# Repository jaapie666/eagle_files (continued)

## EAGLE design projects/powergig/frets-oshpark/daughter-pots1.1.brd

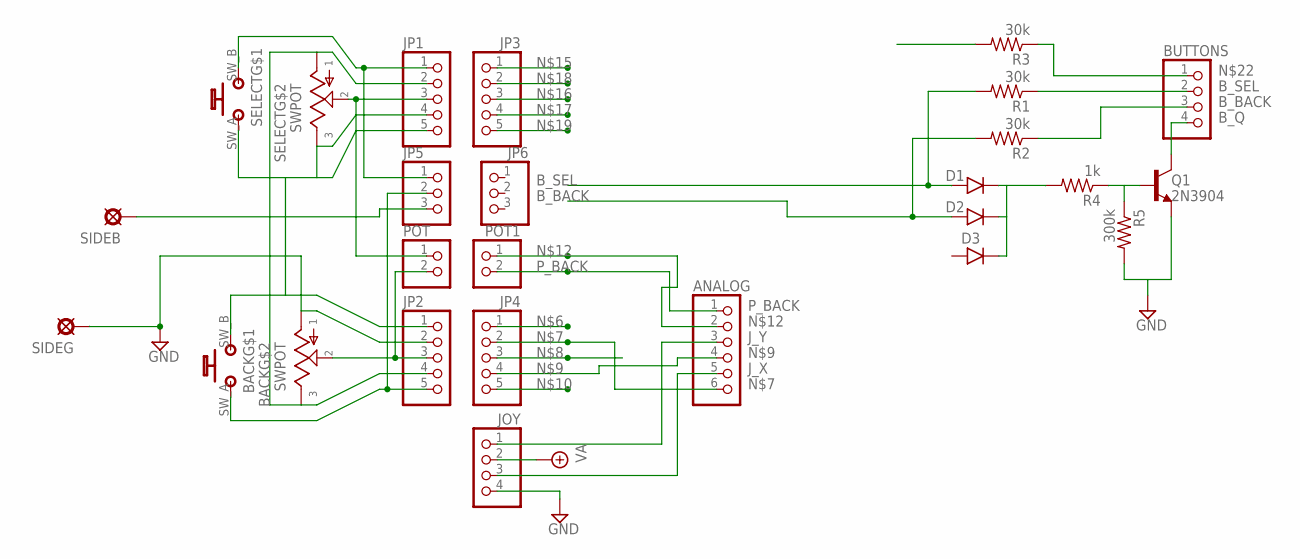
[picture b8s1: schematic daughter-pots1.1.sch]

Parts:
ANALOG: PINHD-1X6; 1X06
BACK: SWPOT
BUTTONS: PINHD-1X4; 1X04
D1: 1N4148-3; DO35-3
D2: 1N4148-2; DO35-2
D3: 1N4148-4; DO35-4
JOY: PINHD-1X4; 1X04
JP1, JP2, JP3, JP4: PINHD-1X5; 1X05
JP5, JP6: PINHD-1X3; 1X03
POT, POT1: PINHD-1X2; 1X02
Q1: 2N3904; TO92-
R1, R2, R3: 30k; R0207/3
R4: 1k; R0207/3
R5: 300k; R0207/1V
SELECT: SWPOT
SIDEB: PAD; SQUARE
SIDEG: PAD; SQUARE

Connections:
B_BACK: D2.A, R2.2
B_Q: BUTTONS.4, Q1.1 (C)
B_SEL: D1.A, R1.2
GND: BACK.POT_B, BACK.SW_B (B_B), JOY.4, JP1.4, JP1.5, JP2.1, JP2.2, Q1.3 (E), R5.2, SELECT.POT_A, SELECT.SW_A (B_A), SIDEG.1
J_X: ANALOG.5, JOY.3
J_Y: ANALOG.3, JOY.1
unnamed: Q1.2 (B), R4.1, R5.1
unnamed: BUTTONS.2, R1.1
unnamed: BUTTONS.3, R2.1
unnamed: D1.C, D2.C, D3.C, R4.2
unnamed: BUTTONS.1, R3.1
unnamed: ANALOG.6, JP4.2
unnamed: ANALOG.4, JP4.4
unnamed: BACK.POT_W, JP2.3, POT.2
unnamed: ANALOG.2, POT1.1
unnamed: JP1.1, JP5.1, SELECT.SW_B (B_B)
unnamed: BACK.SW_A (B_A), JP2.5, JP5.2
unnamed: BACK.POT_A, JP1.2, JP2.4, SELECT.POT_B
unnamed: JP5.3, SIDEB.1
P_BACK: ANALOG.1, POT1.2
P_SEL: JP1.3, POT.1, SELECT.POT_W
VA: JOY.2

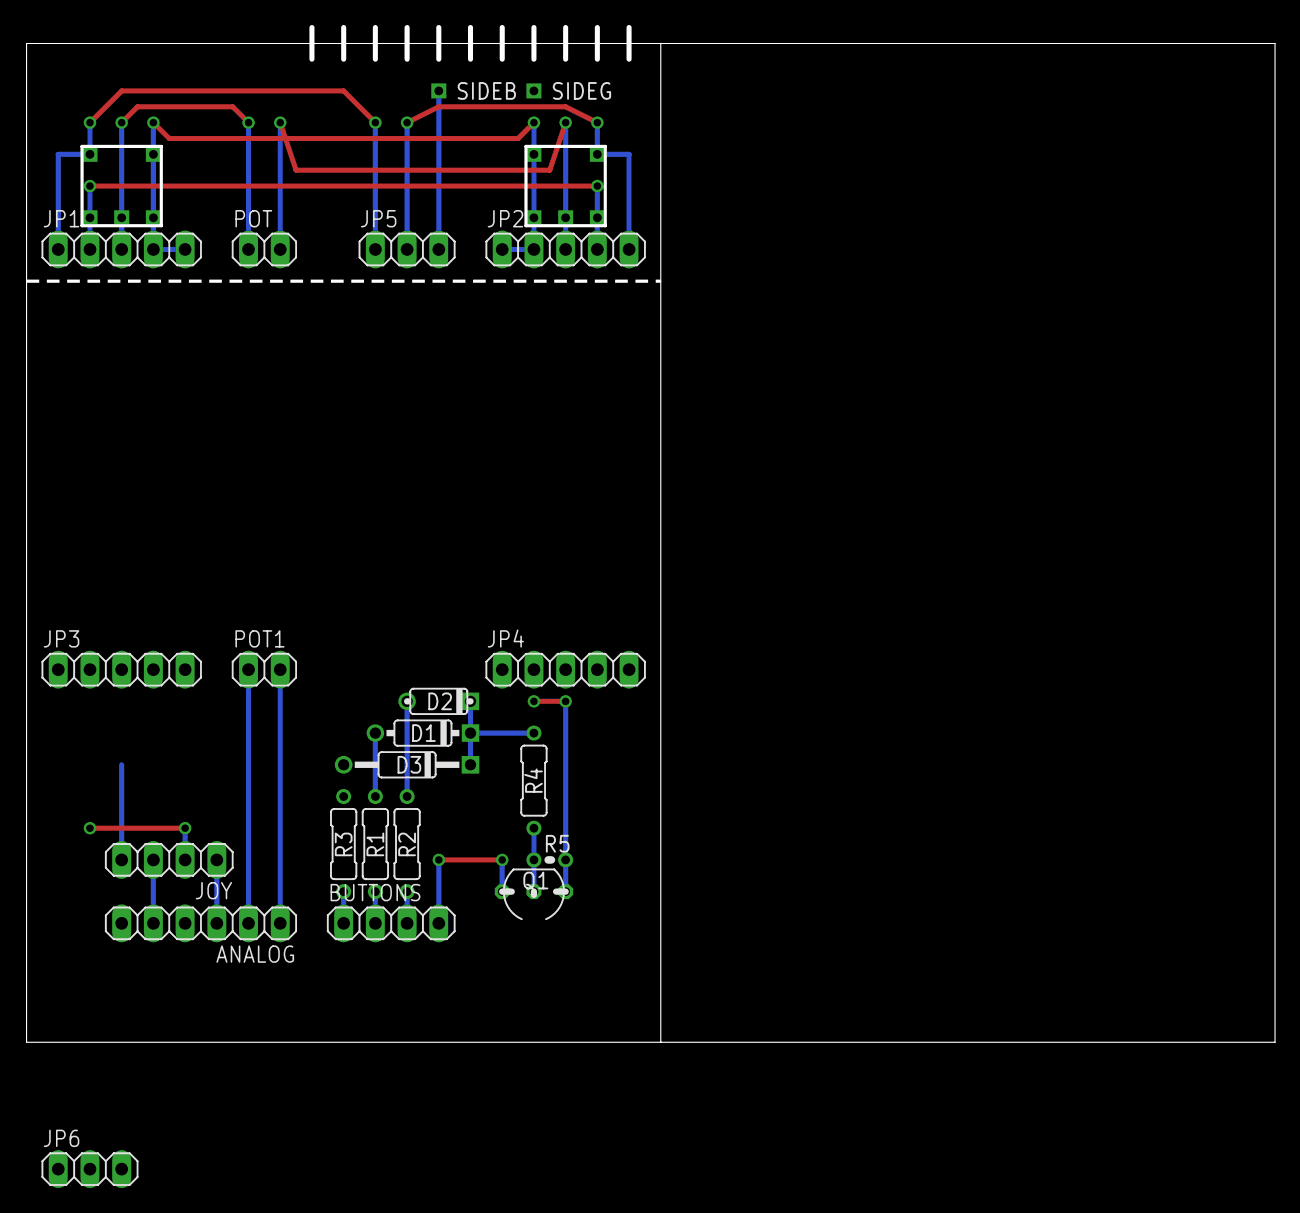
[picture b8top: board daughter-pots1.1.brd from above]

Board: 2 copper layers, 100.0 x 81.3 mm, 24 parts (0 on the bottom side), 21 nets.
